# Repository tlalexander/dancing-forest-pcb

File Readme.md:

PCB design files for The Dancing Forest, an interactive dynamic social art space

Please see https://www.thedancingforest.art/ for more info.

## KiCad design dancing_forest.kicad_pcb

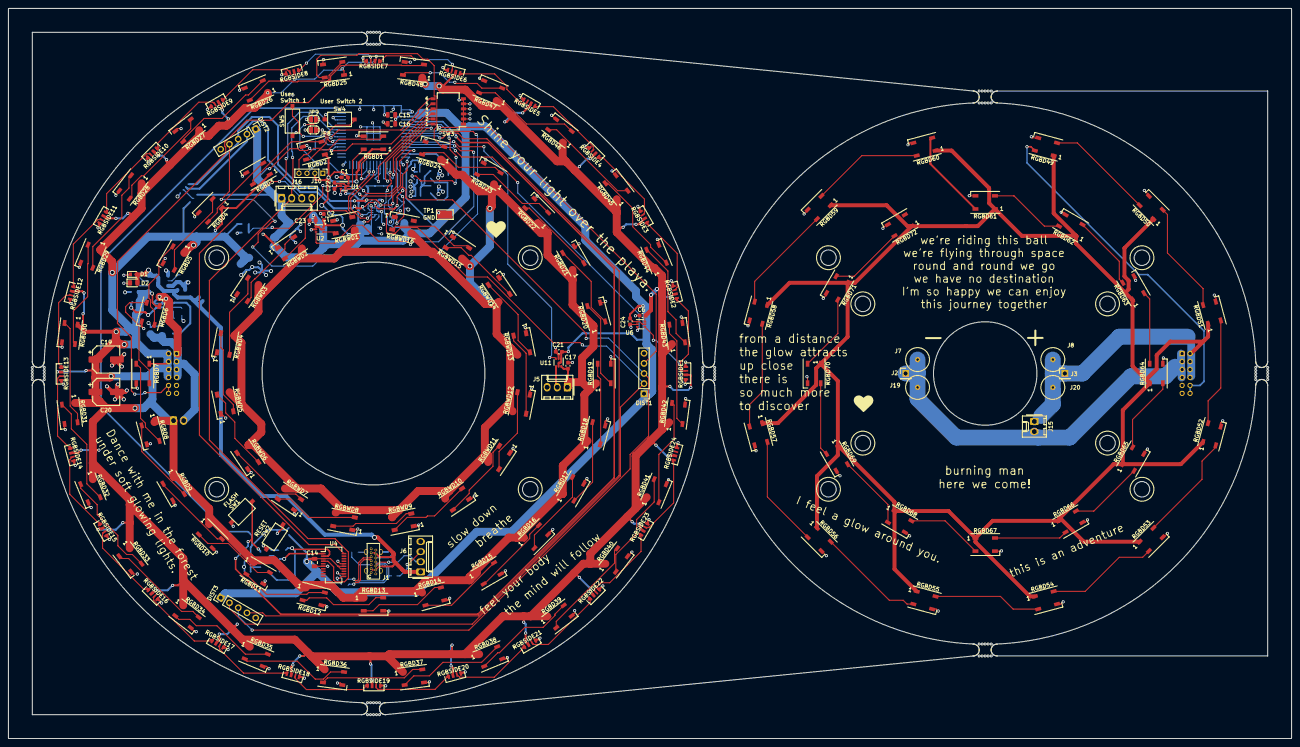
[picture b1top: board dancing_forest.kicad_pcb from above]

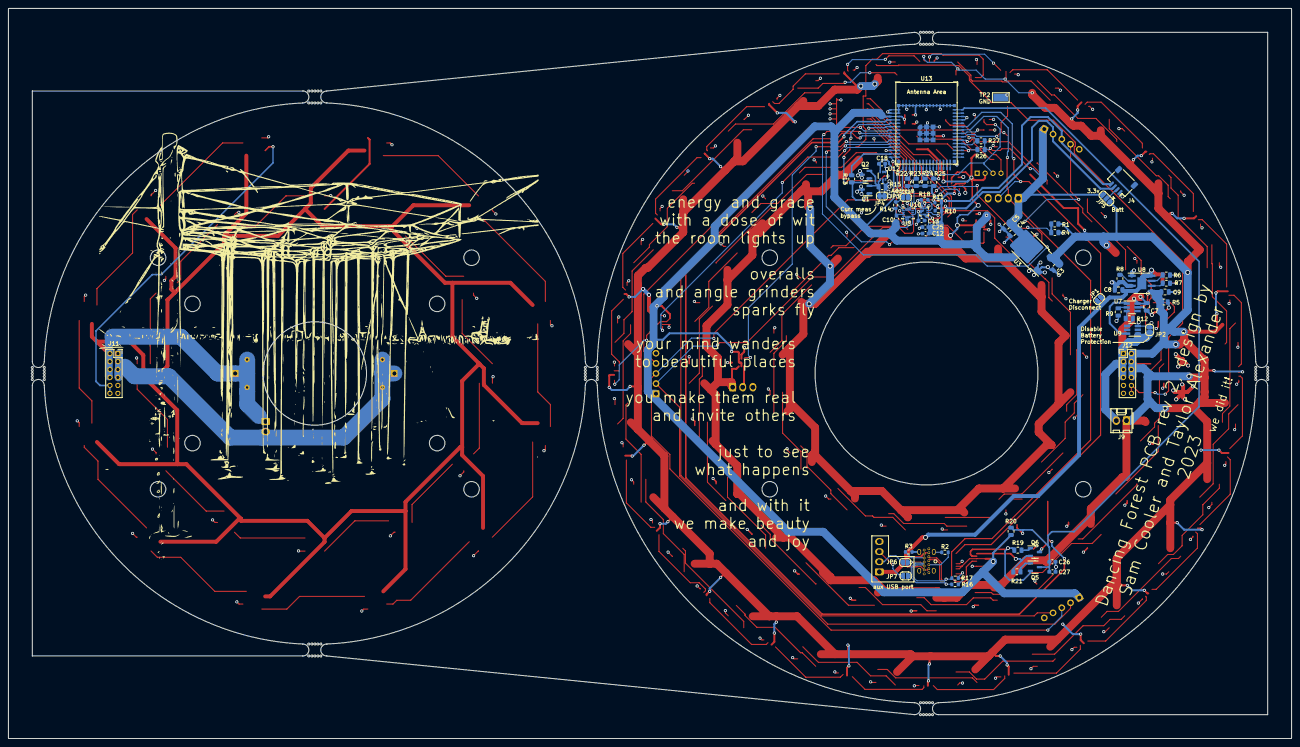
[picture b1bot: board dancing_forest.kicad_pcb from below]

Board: 4 copper layers, 322.5 x 183.5 mm, 238 parts (64 on the bottom side), 178 nets.

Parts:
C1, C2, C6, C10, C13, C17, C18, C21, C22, C23, C24, C25, C26: 0.1uF; C_0603_1608Metric
C3, C4, C5, C9, C16: 10u; C_0805_2012Metric
C7, C8, C14, C15: 0.1uF; C_0805_2012Metric
C12, C27: 1u; C_0603_1608Metric
C19, C20: 470uF 16V; CP_Elec_6.3x7.7
D1: RED; LED_0603_1608Metric
D2: GREEN; LED_0805_2012Metric
DIST1, DIST2, DIST3: Conn_01x05; 5_pin
H1, H2, H3, H4, H5, H6, H7, H8: MountingHole; MountingHole_3.2mm_Plastite_#4
H9: MountingHole_3.2mm_Plastite_#4; H9
H10: MountingHole_3.2mm_Plastite_#4; H10
H11: MountingHole_3.2mm_Plastite_#4; H11
H12: MountingHole_3.2mm_Plastite_#4; H12
J1: USB_C_Receptacle_USB2.0; 918-468K2029E50000
J2, J3: Conn_01x01; PinHeader_1x01_P2.54mm_Vertical
J4: SM04B-SRSS-TB(LF)(SN); JST_SH_SM04B-SRSS-TB_1x04-1MP_P1.00mm_Horizontal
J5: Conn_01x03; Molex_KK-254_AE-6410-03A_1x03_P2.54mm_Vertical
J6, J16: Conn_01x04; Molex_KK-254_AE-6410-04A_1x04_P2.54mm_Vertical
J7, J8, J19, J20: Conn_01x01; spring_F6-6-4-0.4Z
J9, J15: Conn_01x02; Molex_KK-254_AE-6410-02A_1x02_P2.54mm_Vertical
J10: Conn_01x04; PinHeader_1x04_P2.00mm_Vertical
J11: Upper Connector; PinSocket_2x06_P2.00mm_Vertical
J12: Lower Connector; PinHeader_2x06_P2.00mm_Vertical
JP1, JP2, JP3, JP4, JP6, JP7, JP8, JP9: SolderJumper_2_Open; SolderJumper-2_P1.3mm_Open_RoundedPad1.0x1.5mm
JP5: SolderJumper_3_Open; SolderJumper-3_P1.3mm_Open_RoundedPad1.0x1.5mm
Q1, Q2: AO3400A; SOT-23
Q5, Q6: Q_NPN_BEC; SOT-23-3
R1, R4, R19, R20, R21, R22, R23, R24, R25, R26, R27: 10k 0.5%; R_0805_2012Metric
R2, R3, R10, R11, R14, R18: 5.1k; R_0603_1608Metric
R5, R13: 100; R_0805_2012Metric
R6, R7, R9: 1k; R_0805_2012Metric
R8: 1.2k; R_0805_2012Metric
R12: 0R; R_0805_2012Metric
R15: 0.010 R; R_0805_2012Metric
R16, R17: 27; R_0603_1608Metric
RGBD1, RGBD2, RGBD3, RGBD4, RGBD5, RGBD6, RGBD7, RGBD8, RGBD9, RGBD10, RGBD11, RGBD12, RGBD13, RGBD14, RGBD15, RGBD16, RGBD17, RGBD18, RGBD19, RGBD20, RGBD21, RGBD22, RGBD23, RGBD24, RGBD25, RGBD26, RGBD27, RGBD28, RGBD29, RGBD30, RGBD31, RGBD32, RGBD33, RGBD34, RGBD35, RGBD36, RGBD37, RGBD38, RGBD39, RGBD40, RGBD41, RGBD42, RGBD43, RGBD44, RGBD45, RGBD46, RGBD47, RGBD48, RGBD49, RGBD50, RGBD51, RGBD52, RGBD53, RGBD54, RGBD55, RGBD56, RGBD57, RGBD58, RGBD59, RGBD60, RGBD61, RGBD62, RGBD63, RGBD64, RGBD65, RGBD66, RGBD67, RGBD68, RGBD69, RGBD70, RGBD71, RGBD72: WS2812B; LED_WS2812B_PLCC4_5.0x5.0mm_P3.2mm
RGBSIDE1, RGBSIDE2, RGBSIDE3, RGBSIDE4, RGBSIDE5, RGBSIDE6, RGBSIDE7, RGBSIDE8, RGBSIDE9, RGBSIDE10, RGBSIDE11, RGBSIDE12, RGBSIDE13, RGBSIDE14, RGBSIDE15, RGBSIDE16, RGBSIDE17, RGBSIDE18, RGBSIDE19, RGBSIDE20, RGBSIDE21, RGBSIDE22, RGBSIDE23, RGBSIDE24: SK6812-SIDE; SK6812SIDE
RGBWD1, RGBWD2, RGBWD3, RGBWD4, RGBWD5, RGBWD6, RGBWD7, RGBWD8, RGBWD9, RGBWD10, RGBWD11, RGBWD12, RGBWD13, RGBWD14, RGBWD15, RGBWD16: SK6812-RGBW; LED_SK6812_PLCC4_5.0x5.0mm_P3.2mm
SW1, SW2, SW4, SW5: SW_MEC_5G; SW_TS_1101_C_W
SW3: CONFIG SWITCH; SW_DIP_SPSTx06_Slide_KingTek_DSHP06TS_W7.62mm_P1.27mm
TP1, TP2: TestPoint; TestPoint_Keystone_5019_Minature
U1, U2, U6, U11: TXS0101DCKR; SOT-363_SC-70-6
U3: LD1086DT33TR; TO-252-2
U4: FT231XS; SSOP-20_3.9x8.7mm_P0.635mm
U5: LSM6DS3; LGA-14_3x2.5mm_P0.5mm_LayoutBorder3x4y
U7: DW01; SOT-23-6_Handsoldering
U8: TP4056; SOIC-8-1EP_3.9x4.9mm_P1.27mm_EP2.29x3mm
U9: FS8205A; SOT-23-6_Handsoldering
U10: LIS3MDL; LGA-12_2x2mm_P0.5mm
U12: INA199xxDCK; SOT-363_SC-70-6
U13: ESP32-S3-MINI-1-N8; ESP32-S3-MINI-1-breakout
mousebite1: VAL**; mousebite1
mousebite2: VAL**; mousebite2
mousebite3: VAL**; mousebite3
mousebite4: VAL**; mousebite4
mousebite5: VAL**; mousebite5
mousebite6: VAL**; mousebite6
mousebite7: VAL**; mousebite7

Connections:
+3V3: C4.1, C5.1, C10.1, C12.1, C14.1, C15.2, C16.2, C18.1, C21.1, C22.1, C23.1, C24.1, C25.1, DIST1.1, DIST2.1, DIST3.1, J16.1, JP3.1 (A), JP5.3 (B), R10.1, R11.2, R20.2, R22.1, R23.1, R24.1, R25.1, R26.1, R27.1, U1.1 (VCCA), U1.5 (OE), U2.1 (VCCA), U2.5 (OE), U3.2 (OUT), U4.3 (VCCIO), U4.14 (~RESET), U4.15 (VCC), U5.5 (VDDIO), U5.8 (VDD), U5.12 (CS), U6.1 (VCCA), U6.5 (OE), U10.5 (Vdd), U10.6 (Vdd_IO), U10.10 (~CS), U11.1 (VCCA), U11.5 (OE), U12.3 (V+), U13.3 (3V3)
+BATT: C1.1, C2.1, C3.1, C6.1, C9.1, C17.1, C19.1, C20.1, J3.1, J5.1, J8.1, J9.1, J10.2, J11.2, J11.4, J11.6, J11.8, J12.2, J12.4, J12.6, J12.8, J15.1, J20.1, JP5.1 (A), R1.1, R5.1, RGBD1.1 (VDD), RGBD2.1 (VDD), RGBD3.1 (VDD), RGBD4.1 (VDD), RGBD5.1 (VDD), RGBD6.1 (VDD), RGBD7.1 (VDD), RGBD8.1 (VDD), RGBD9.1 (VDD), RGBD10.1 (VDD), RGBD11.1 (VDD), RGBD12.1 (VDD), RGBD13.1 (VDD), RGBD14.1 (VDD), RGBD15.1 (VDD), RGBD16.1 (VDD), RGBD17.1 (VDD), RGBD18.1 (VDD), RGBD19.1 (VDD), RGBD20.1 (VDD), RGBD21.1 (VDD), RGBD22.1 (VDD), RGBD23.1 (VDD), RGBD24.1 (VDD), RGBD25.1 (VDD), RGBD26.1 (VDD), RGBD27.1 (VDD), RGBD28.1 (VDD), RGBD29.1 (VDD), RGBD30.1 (VDD), RGBD31.1 (VDD), RGBD32.1 (VDD), RGBD33.1 (VDD), RGBD34.1 (VDD), RGBD35.1 (VDD), RGBD36.1 (VDD), RGBD37.1 (VDD), RGBD38.1 (VDD), RGBD39.1 (VDD), RGBD40.1 (VDD), RGBD41.1 (VDD), RGBD42.1 (VDD), RGBD43.1 (VDD), RGBD44.1 (VDD), RGBD45.1 (VDD), RGBD46.1 (VDD), RGBD47.1 (VDD), RGBD48.1 (VDD), RGBD49.1 (VDD), RGBD50.1 (VDD), RGBD51.1 (VDD), RGBD52.1 (VDD), RGBD53.1 (VDD), RGBD54.1 (VDD), RGBD55.1 (VDD), RGBD56.1 (VDD), RGBD57.1 (VDD), RGBD58.1 (VDD), RGBD59.1 (VDD), RGBD60.1 (VDD), RGBD61.1 (VDD), RGBD62.1 (VDD), RGBD63.1 (VDD), RGBD64.1 (VDD), RGBD65.1 (VDD), RGBD66.1 (VDD), RGBD67.1 (VDD), RGBD68.1 (VDD), RGBD69.1 (VDD), RGBD70.1 (VDD), RGBD71.1 (VDD), RGBD72.1 (VDD), RGBSIDE1.2 (VDD), RGBSIDE2.2 (VDD), RGBSIDE3.2 (VDD), RGBSIDE4.2 (VDD), RGBSIDE5.2 (VDD), RGBSIDE6.2 (VDD), RGBSIDE7.2 (VDD), RGBSIDE8.2 (VDD), RGBSIDE9.2 (VDD), RGBSIDE10.2 (VDD), RGBSIDE11.2 (VDD), RGBSIDE12.2 (VDD), RGBSIDE13.2 (VDD), RGBSIDE14.2 (VDD), RGBSIDE15.2 (VDD), RGBSIDE16.2 (VDD), RGBSIDE17.2 (VDD), RGBSIDE18.2 (VDD), RGBSIDE19.2 (VDD), RGBSIDE20.2 (VDD), RGBSIDE21.2 (VDD), RGBSIDE22.2 (VDD), RGBSIDE23.2 (VDD), RGBSIDE24.2 (VDD), RGBWD1.3 (VDD), RGBWD2.3 (VDD), RGBWD3.3 (VDD), RGBWD4.3 (VDD), RGBWD5.3 (VDD), RGBWD6.3 (VDD), RGBWD7.3 (VDD), RGBWD8.3 (VDD), RGBWD9.3 (VDD), RGBWD10.3 (VDD), RGBWD11.3 (VDD), RGBWD12.3 (VDD), RGBWD13.3 (VDD), RGBWD14.3 (VDD), RGBWD15.3 (VDD), RGBWD16.3 (VDD), U1.6 (VCCB), U2.6 (VCCB), U3.3 (IN), U6.6 (VCCB), U8.5 (BAT), U11.6 (VCCB)
/G1: U7.1 (OD), U9.6 (G1)
/G2: R12.2, U9.4 (G2)
/OC: R12.1, U7.3 (OC)
/USB_DN: R17.2, U4.12 (USBDM)
/USB_DP: R16.2, U4.11 (USBDP)
ADDY_1: R22.2, SW3.12, U13.19 (GPIO15/U0RTS/ADC2_CH4/XTAL_32K_P)
ADDY_2: R23.2, SW3.11, U13.20 (GPIO16/U0CTS/ADC2_CH5/XTAL_32K_NH5)
ADDY_3: R24.2, SW3.10, U13.21 (GPIO17/U1TXD/ADC2_CH6)
ADDY_4: R25.2, SW3.9, U13.22 (GPIO18/U1RXD/ADC2_CH7/CLK_OUT3)
ADDY_5: R26.2, SW3.8, U13.34 (GPIO38/FSPIWP/SUBSPIWP)
ADDY_6: R27.2, SW3.7, U13.35 (MTCK/GPIO39/CLK_OUT3/SUBSPICS1)
AUX1: J10.3, JP9.2 (B), U13.25 (GPIO21)
AUX2: J10.4, JP8.2 (B), U13.38 (MTMS/GPIO42)
BAT-: C7.2, J2.1, J7.1, J9.2, J11.1, J11.3, J11.5, J11.7, J12.1, J12.3, J12.5, J12.7, J15.2, J19.1, JP2.1 (A), U7.6 (GND), U9.1 (S1)
BATT_MEASURE: R1.2, R4.1, U13.6 (GPIO2/TOUCH2/ADC1_CH1)
CURRENT_MEASURE: U12.6, U13.5 (GPIO1/TOUCH1/ADC1_CH0)
DN: J6.2, JP6.2 (B)
DP: J6.3, JP7.2 (B)
DRDY: U10.8 (DRDY), U13.23 (GPIO19/U1RTS/ADC2_CH8/CLK_OUT2/USB_D-)
EN: C26.1, C27.1, Q5.3 (C), R20.1, SW2.2, U13.45 (EN)
ESP_RX: J16.3, U4.20 (TXD), U13.40 (U0RXD/GPIO44/CLK_OUT2)
ESP_TX: J16.2, U4.4 (RXD), U13.39 (U0TXD/GPIO43/CLK_OUT1)
EXT_LED: U11.3 (A), U13.10 (GPIO6/TOUCH6/ADC1_CH5)
GND: C1.2, C2.2, C3.2, C4.2, C5.2, C6.2, C8.2, C9.2, C10.2, C12.2, C13.2, C14.2, C15.1, C16.1, C17.2, C18.2, C19.2, C20.2, C21.2, C22.2, C23.2, C24.2, C25.2, C26.2, C27.2, DIST1.5, DIST2.5, DIST3.5, J1.A1 (GND), J1.A12 (GND), J1.B1 (GND), J1.B12 (GND), J1.S1 (SHIELD), J4.1, J6.4, J10.1, J16.4, JP2.2 (B), JP4.1 (A), JP8.1 (A), JP9.1 (A), R2.1, R3.2, R4.2, R8.2, R9.1, R14.1, R15.2, R18.1, SW1.1, SW2.1, SW3.1, SW3.2, SW3.3, SW3.4, SW3.5, SW3.6, SW4.1, SW5.1, TP1.1, TP2.1, U1.2 (GND), U2.2 (GND), U3.1 (ADJ/GND), U4.6 (GND), U4.16 (GND), U5.2 (SDX), U5.3 (SCX), U5.6 (GND), U5.7 (GND), U6.2 (GND), U8.1 (TEMP), U8.3 (GND), U9.3 (S2), U10.2 (GND), U10.3 (GND), U10.12 (GND), U11.2 (GND), U12.1 (REF), U12.2 (GND), U12.5 (-), U13.1 (GND), U13.2 (GND), U13.42 (GND), U13.43 (GND), U13.46 (GND), U13.47 (GND), U13.48 (GND), U13.49 (GND), U13.50 (GND), U13.51 (GND), U13.52 (GND), U13.53 (GND), U13.54 (GND), U13.55 (GND), U13.56 (GND), U13.57 (GND), U13.58 (GND), U13.59 (GND), U13.60 (GND), U13.61 (GND), U13.62 (GND), U13.63 (GND), U13.64 (GND), U13.65 (GND)
INT: U10.7 (INT), U13.24 (GPIO20/U1CTS/ADC2_CH9/CLK_OUT1/USB_D+)
INT1: U5.4 (INT1), U13.17 (GPIO13/TOUCH13/ADC2_CH2/FSPIQ/FSPIIO7/S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)
INT2: U5.9 (INT2), U13.18 (GPIO14/TOUCH14/ADC2_CH3/FSPIWP/FSPIDQS/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)
IO0: Q6.3 (C), SW1.2, U13.4 (GPIO0/BOOT)
LEDGND: J5.3, J11.9, J11.11, J12.9, J12.11, Q1.3 (D), Q2.3 (D), RGBD1.3 (VSS), RGBD2.3 (VSS), RGBD3.3 (VSS), RGBD4.3 (VSS), RGBD5.3 (VSS), RGBD6.3 (VSS), RGBD7.3 (VSS), RGBD8.3 (VSS), RGBD9.3 (VSS), RGBD10.3 (VSS), RGBD11.3 (VSS), RGBD12.3 (VSS), RGBD13.3 (VSS), RGBD14.3 (VSS), RGBD15.3 (VSS), RGBD16.3 (VSS), RGBD17.3 (VSS), RGBD18.3 (VSS), RGBD19.3 (VSS), RGBD20.3 (VSS), RGBD21.3 (VSS), RGBD22.3 (VSS), RGBD23.3 (VSS), RGBD24.3 (VSS), RGBD25.3 (VSS), RGBD26.3 (VSS), RGBD27.3 (VSS), RGBD28.3 (VSS), RGBD29.3 (VSS), RGBD30.3 (VSS), RGBD31.3 (VSS), RGBD32.3 (VSS), RGBD33.3 (VSS), RGBD34.3 (VSS), RGBD35.3 (VSS), RGBD36.3 (VSS), RGBD37.3 (VSS), RGBD38.3 (VSS), RGBD39.3 (VSS), RGBD40.3 (VSS), RGBD41.3 (VSS), RGBD42.3 (VSS), RGBD43.3 (VSS), RGBD44.3 (VSS), RGBD45.3 (VSS), RGBD46.3 (VSS), RGBD47.3 (VSS), RGBD48.3 (VSS), RGBD49.3 (VSS), RGBD50.3 (VSS), RGBD51.3 (VSS), RGBD52.3 (VSS), RGBD53.3 (VSS), RGBD54.3 (VSS), RGBD55.3 (VSS), RGBD56.3 (VSS), RGBD57.3 (VSS), RGBD58.3 (VSS), RGBD59.3 (VSS), RGBD60.3 (VSS), RGBD61.3 (VSS), RGBD62.3 (VSS), RGBD63.3 (VSS), RGBD64.3 (VSS), RGBD65.3 (VSS), RGBD66.3 (VSS), RGBD67.3 (VSS), RGBD68.3 (VSS), RGBD69.3 (VSS), RGBD70.3 (VSS), RGBD71.3 (VSS), RGBD72.3 (VSS), RGBSIDE1.4 (VSS), RGBSIDE2.4 (VSS), RGBSIDE3.4 (VSS), RGBSIDE4.4 (VSS), RGBSIDE5.4 (VSS), RGBSIDE6.4 (VSS), RGBSIDE7.4 (VSS), RGBSIDE8.4 (VSS), RGBSIDE9.4 (VSS), RGBSIDE10.4 (VSS), RGBSIDE11.4 (VSS), RGBSIDE12.4 (VSS), RGBSIDE13.4 (VSS), RGBSIDE14.4 (VSS), RGBSIDE15.4 (VSS), RGBSIDE16.4 (VSS), RGBSIDE17.4 (VSS), RGBSIDE18.4 (VSS), RGBSIDE19.4 (VSS), RGBSIDE20.4 (VSS), RGBSIDE21.4 (VSS), RGBSIDE22.4 (VSS), RGBSIDE23.4 (VSS), RGBSIDE24.4 (VSS), RGBWD1.1 (VSS), RGBWD2.1 (VSS), RGBWD3.1 (VSS), RGBWD4.1 (VSS), RGBWD5.1 (VSS), RGBWD6.1 (VSS), RGBWD7.1 (VSS), RGBWD8.1 (VSS), RGBWD9.1 (VSS), RGBWD10.1 (VSS), RGBWD11.1 (VSS), RGBWD12.1 (VSS), RGBWD13.1 (VSS), RGBWD14.1 (VSS), RGBWD15.1 (VSS), RGBWD16.1 (VSS)
LED_FET: R13.2, U13.14 (GPIO10/TOUCH10/ADC1_CH9/FSPICS0/FSPIIO4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)
unnamed: D1.1 (K), R6.1
unnamed: D2.1 (K), R7.1
unnamed: J1.A5 (CC1), R2.2
unnamed: J1.B5 (CC2), R3.1
unnamed: J4.2, JP5.2 (C)
unnamed: J5.2, U11.4 (B)
unnamed: JP3.2 (B), R14.2, U5.1 (SDO/SA0)
unnamed: JP4.2 (B), Q1.2 (S), Q2.2 (S), R15.1, U12.4 (+)
unnamed: Q1.1 (G), Q2.1 (G), R13.1
unnamed: Q5.1 (B), R21.2
unnamed: Q6.1 (B), R19.1
unnamed: RGBD1.4 (DIN), U1.4 (B)
unnamed: RGBD1.2 (DOUT), RGBD2.4 (DIN)
unnamed: RGBD2.2 (DOUT), RGBD3.4 (DIN)
unnamed: RGBD3.2 (DOUT), RGBD4.4 (DIN)
unnamed: RGBD4.2 (DOUT), RGBD5.4 (DIN)
unnamed: RGBD5.2 (DOUT), RGBD6.4 (DIN)
unnamed: RGBD6.2 (DOUT), RGBD7.4 (DIN)
unnamed: RGBD7.2 (DOUT), RGBD8.4 (DIN)
unnamed: RGBD8.2 (DOUT), RGBD9.4 (DIN)
unnamed: RGBD9.2 (DOUT), RGBD10.4 (DIN)
unnamed: RGBD10.2 (DOUT), RGBD11.4 (DIN)
unnamed: RGBD11.2 (DOUT), RGBD12.4 (DIN)
unnamed: RGBD12.2 (DOUT), RGBD13.4 (DIN)
unnamed: RGBD13.2 (DOUT), RGBD14.4 (DIN)
unnamed: RGBD14.2 (DOUT), RGBD15.4 (DIN)
unnamed: RGBD15.2 (DOUT), RGBD16.4 (DIN)
unnamed: RGBD16.2 (DOUT), RGBD17.4 (DIN)
unnamed: RGBD17.2 (DOUT), RGBD18.4 (DIN)
unnamed: RGBD18.2 (DOUT), RGBD19.4 (DIN)
unnamed: RGBD19.2 (DOUT), RGBD20.4 (DIN)
unnamed: RGBD20.2 (DOUT), RGBD21.4 (DIN)
unnamed: RGBD21.2 (DOUT), RGBD22.4 (DIN)
unnamed: RGBD22.2 (DOUT), RGBD23.4 (DIN)
unnamed: RGBD23.2 (DOUT), RGBD24.4 (DIN)
unnamed: RGBD24.2 (DOUT), RGBD25.4 (DIN)
unnamed: RGBD25.2 (DOUT), RGBD26.4 (DIN)
unnamed: RGBD26.2 (DOUT), RGBD27.4 (DIN)
unnamed: RGBD27.2 (DOUT), RGBD28.4 (DIN)
unnamed: RGBD28.2 (DOUT), RGBD29.4 (DIN)
unnamed: RGBD29.2 (DOUT), RGBD30.4 (DIN)
unnamed: RGBD30.2 (DOUT), RGBD31.4 (DIN)
unnamed: RGBD31.2 (DOUT), RGBD32.4 (DIN)
unnamed: RGBD32.2 (DOUT), RGBD33.4 (DIN)
unnamed: RGBD33.2 (DOUT), RGBD34.4 (DIN)
unnamed: RGBD34.2 (DOUT), RGBD35.4 (DIN)
unnamed: RGBD35.2 (DOUT), RGBD36.4 (DIN)
unnamed: RGBD36.2 (DOUT), RGBD37.4 (DIN)
unnamed: RGBD37.2 (DOUT), RGBD38.4 (DIN)
unnamed: RGBD38.2 (DOUT), RGBD39.4 (DIN)
unnamed: RGBD39.2 (DOUT), RGBD40.4 (DIN)
unnamed: RGBD40.2 (DOUT), RGBD41.4 (DIN)
unnamed: RGBD41.2 (DOUT), RGBD42.4 (DIN)
unnamed: RGBD42.2 (DOUT), RGBD43.4 (DIN)
unnamed: RGBD43.2 (DOUT), RGBD44.4 (DIN)
unnamed: RGBD44.2 (DOUT), RGBD45.4 (DIN)
unnamed: RGBD45.2 (DOUT), RGBD46.4 (DIN)
unnamed: RGBD46.2 (DOUT), RGBD47.4 (DIN)
unnamed: RGBD47.2 (DOUT), RGBD48.4 (DIN)
unnamed: RGBD49.2 (DOUT), RGBD50.4 (DIN)
unnamed: RGBD50.2 (DOUT), RGBD51.4 (DIN)
unnamed: RGBD51.2 (DOUT), RGBD52.4 (DIN)
unnamed: RGBD52.2 (DOUT), RGBD53.4 (DIN)
unnamed: RGBD53.2 (DOUT), RGBD54.4 (DIN)
unnamed: RGBD54.2 (DOUT), RGBD55.4 (DIN)
unnamed: RGBD55.2 (DOUT), RGBD56.4 (DIN)
unnamed: RGBD56.2 (DOUT), RGBD57.4 (DIN)
unnamed: RGBD57.2 (DOUT), RGBD58.4 (DIN)
unnamed: RGBD58.2 (DOUT), RGBD59.4 (DIN)
unnamed: RGBD59.2 (DOUT), RGBD60.4 (DIN)
unnamed: RGBD60.2 (DOUT), RGBD61.4 (DIN)
unnamed: RGBD61.2 (DOUT), RGBD62.4 (DIN)
unnamed: RGBD62.2 (DOUT), RGBD63.4 (DIN)
unnamed: RGBD63.2 (DOUT), RGBD64.4 (DIN)
unnamed: RGBD64.2 (DOUT), RGBD65.4 (DIN)
unnamed: RGBD65.2 (DOUT), RGBD66.4 (DIN)
unnamed: RGBD66.2 (DOUT), RGBD67.4 (DIN)
unnamed: RGBD67.2 (DOUT), RGBD68.4 (DIN)
unnamed: RGBD68.2 (DOUT), RGBD69.4 (DIN)
unnamed: RGBD69.2 (DOUT), RGBD70.4 (DIN)
unnamed: RGBD70.2 (DOUT), RGBD71.4 (DIN)
unnamed: RGBD71.2 (DOUT), RGBD72.4 (DIN)
unnamed: RGBSIDE1.1 (DIN), U6.4 (B)
unnamed: RGBSIDE1.3 (DOUT), RGBSIDE2.1 (DIN)
unnamed: RGBSIDE2.3 (DOUT), RGBSIDE3.1 (DIN)
unnamed: RGBSIDE3.3 (DOUT), RGBSIDE4.1 (DIN)
unnamed: RGBSIDE4.3 (DOUT), RGBSIDE5.1 (DIN)
unnamed: RGBSIDE5.3 (DOUT), RGBSIDE6.1 (DIN)
unnamed: RGBSIDE6.3 (DOUT), RGBSIDE7.1 (DIN)
unnamed: RGBSIDE7.3 (DOUT), RGBSIDE8.1 (DIN)
unnamed: RGBSIDE8.3 (DOUT), RGBSIDE9.1 (DIN)
unnamed: RGBSIDE9.3 (DOUT), RGBSIDE10.1 (DIN)
unnamed: RGBSIDE10.3 (DOUT), RGBSIDE11.1 (DIN)
unnamed: RGBSIDE11.3 (DOUT), RGBSIDE12.1 (DIN)
unnamed: RGBSIDE12.3 (DOUT), RGBSIDE13.1 (DIN)
unnamed: RGBSIDE13.3 (DOUT), RGBSIDE14.1 (DIN)
unnamed: RGBSIDE14.3 (DOUT), RGBSIDE15.1 (DIN)
unnamed: RGBSIDE15.3 (DOUT), RGBSIDE16.1 (DIN)
unnamed: RGBSIDE16.3 (DOUT), RGBSIDE17.1 (DIN)
unnamed: RGBSIDE17.3 (DOUT), RGBSIDE18.1 (DIN)
unnamed: RGBSIDE18.3 (DOUT), RGBSIDE19.1 (DIN)
unnamed: RGBSIDE19.3 (DOUT), RGBSIDE20.1 (DIN)
unnamed: RGBSIDE20.3 (DOUT), RGBSIDE21.1 (DIN)
unnamed: RGBSIDE21.3 (DOUT), RGBSIDE22.1 (DIN)
unnamed: RGBSIDE22.3 (DOUT), RGBSIDE23.1 (DIN)
unnamed: RGBSIDE23.3 (DOUT), RGBSIDE24.1 (DIN)
unnamed: RGBWD1.2 (DIN), U2.4 (B)
unnamed: RGBWD1.4 (DOUT), RGBWD2.2 (DIN)
unnamed: RGBWD2.4 (DOUT), RGBWD3.2 (DIN)
unnamed: RGBWD3.4 (DOUT), RGBWD4.2 (DIN)
unnamed: RGBWD4.4 (DOUT), RGBWD5.2 (DIN)
unnamed: RGBWD5.4 (DOUT), RGBWD6.2 (DIN)
unnamed: RGBWD6.4 (DOUT), RGBWD7.2 (DIN)
unnamed: RGBWD7.4 (DOUT), RGBWD8.2 (DIN)
unnamed: RGBWD8.4 (DOUT), RGBWD9.2 (DIN)
unnamed: RGBWD9.4 (DOUT), RGBWD10.2 (DIN)
unnamed: RGBWD10.4 (DOUT), RGBWD11.2 (DIN)
unnamed: RGBWD11.4 (DOUT), RGBWD12.2 (DIN)
unnamed: RGBWD12.4 (DOUT), RGBWD13.2 (DIN)
unnamed: RGBWD13.4 (DOUT), RGBWD14.2 (DIN)
unnamed: RGBWD14.4 (DOUT), RGBWD15.2 (DIN)
unnamed: RGBWD15.4 (DOUT), RGBWD16.2 (DIN)
unnamed: R9.2, U7.2 (CS)
unnamed: C7.1, R5.2, U7.5 (VCC)
unnamed: R8.1, U8.2 (PROG)
unnamed: R6.2, U8.7 (~CHRG)
unnamed: R7.2, U8.6 (~STDBY)
unnamed: C13.1, U10.4 (C1)
unnamed: R18.2, U10.9 (SDO/SA1)
unnamed: SW5.2, U13.37 (MTDI/GPIO41/CLK_OUT1)
unnamed: SW4.2, U13.36 (MTDO/GPIO40/CLK_OUT2)
RGB-LOWER-OUT: J12.10, J12.12, RGBD48.2 (DOUT)
RGB-UPPER-IN: J11.10, J11.12, RGBD49.4 (DIN)
SCL: DIST1.3, DIST2.3, DIST3.3, J4.4, R11.1, U5.13 (SCL), U10.1 (SCL/SPC), U13.15 (GPIO11/TOUCH11/ADC2_CH0/FSPID/FSPIIO5/S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)
SDA: DIST1.2, DIST2.2, DIST3.2, J4.3, R10.2, U5.14 (SDA), U10.11 (SDA/SDI/SDO), U13.16 (GPIO12/TOUCH12/ADC2_CH1/FSPICLK/FSPIIO6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)
SK6812-RGBW: U2.3 (A), U13.11 (GPIO7/TOUCH7/ADC1_CH6)
SK6812-SIDE: U6.3 (A), U13.12 (GPIO8/TOUCH8/ADC1_CH7/SUBSPICS1)
USB_D+: J1.A6 (D+), J1.B6 (D+), JP7.1 (A), R16.1
USB_D-: J1.A7 (D-), J1.B7 (D-), JP6.1 (A), R17.1
VBUS: C8.1, D1.2 (A), D2.2 (A), J1.A4 (VBUS), J1.A9 (VBUS), J1.B4 (VBUS), J1.B9 (VBUS), J6.1, JP1.1 (A), JP1.2 (B), U8.4 (VCC), U8.8 (CE), U8.9 (PP)
WS2812: U1.3 (A), U13.13 (GPIO9/TOUCH9/ADC1_CH8/FSPIHD/SUBSPIHD)
XSHUT1: DIST1.4, U13.7 (GPIO3/TOUCH3/ADC1_CH2)
XSHUT2: DIST2.4, U13.8 (GPIO4/TOUCH4/ADC1_CH3)
XSHUT3: DIST3.4, U13.9 (GPIO5/TOUCH5/ADC1_CH4)
~DTR: Q6.2 (E), R21.1, U4.1 (~DTR)
~RTS: Q5.2 (E), R19.2, U4.2 (~RTS)

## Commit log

2023-07-04 initial commit - first version of the dancing forest!
2023-08-24 Updated files including PCB fix. Added license.
2023-08-24 remove some unnecessary files
2023-08-24 add readme
